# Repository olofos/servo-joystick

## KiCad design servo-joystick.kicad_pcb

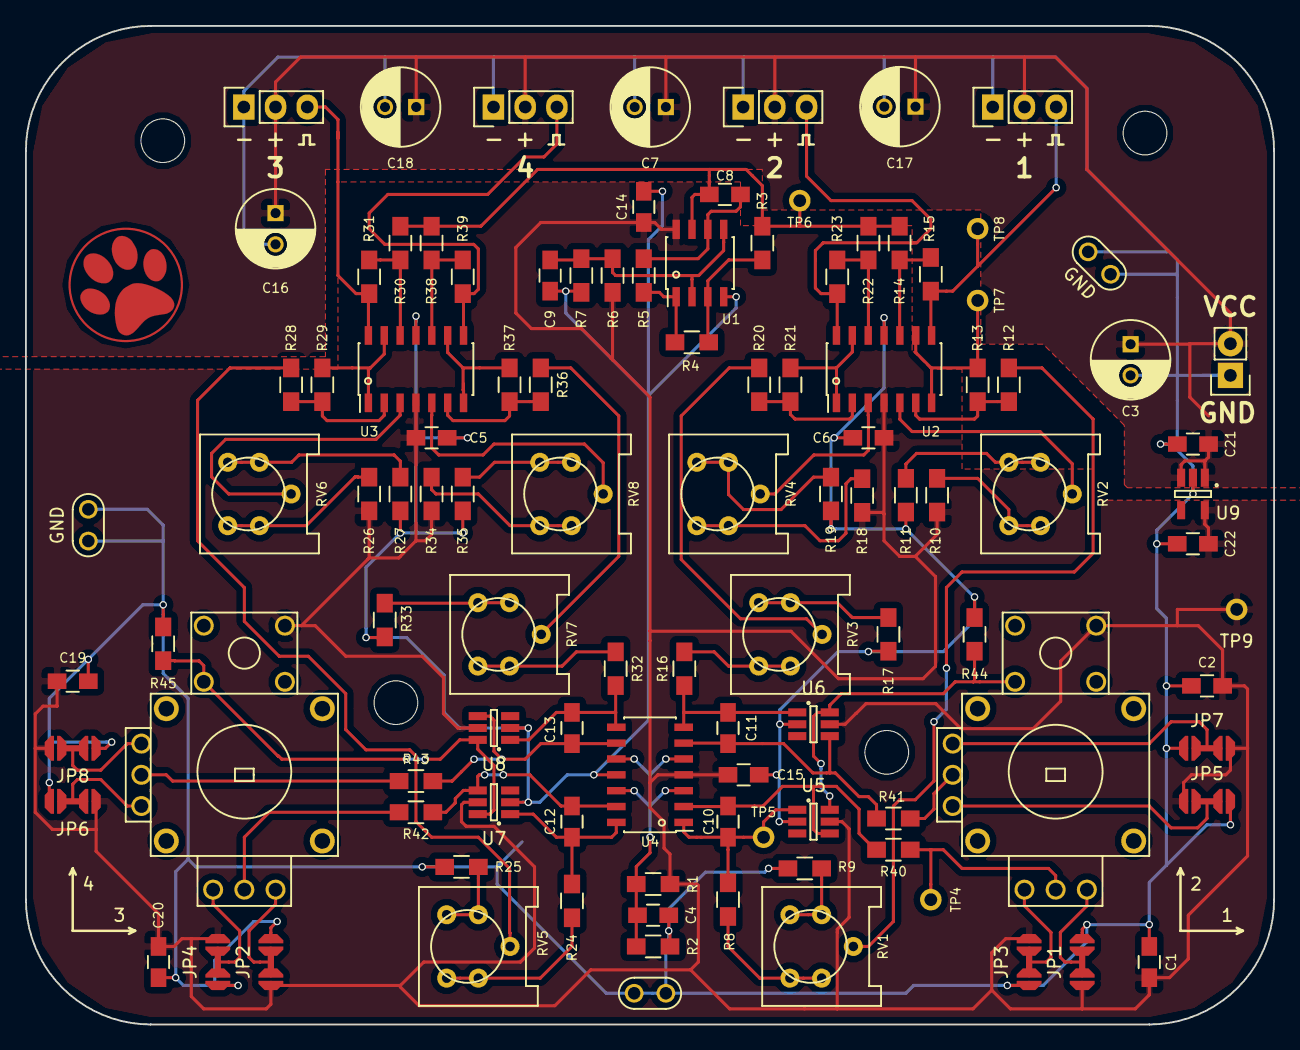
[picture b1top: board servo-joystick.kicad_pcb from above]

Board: 2 copper layers, 100.0 x 80.0 mm, 112 parts (0 on the bottom side), 71 nets.

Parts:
C1, C2, C4, C5, C6, C9, C14, C15, C19, C20: 1u; C_0805_HandSoldering
C3, C7, C16, C17, C18: 100u; C_Radial_D6.3_L11.2_P2.5
C8, C10, C11, C12, C13: 100n; C_0805_HandSoldering
C21, C22: 2u2; C_0805_HandSoldering
JP1, JP2, JP3, JP4, JP5, JP6, JP7, JP8: JUMPER-3
MH6, MH6#2, MH6#3, MH6#4: MOUNTING_HOLE; MH-M3
P1: CONN_01X02; Pin_Header_Straight_1x02
P2, P3, P4, P5: CONN_01X03; Pin_Header_Straight_1x03
R1, R2, R3, R6, R7, R44, R45: 1k2; R_0805_HandSoldering
R4: 3k; R_0805_HandSoldering
R5, R12, R13, R15, R20, R21, R23, R28, R29, R31, R36, R37, R39: 150k; R_0805_HandSoldering
R8, R10, R16, R18, R24, R26, R32, R34: 30k; R_0805_HandSoldering
R9, R14, R17, R22, R25, R30, R33, R38: 470; R_0805_HandSoldering
R11, R19, R27, R35: 15k; R_0805_HandSoldering
R40, R41, R42, R43: 6M8; R_0805_HandSoldering
RV1, RV3, RV5, RV7: 100; Potentiometer_Bourns_3386P
RV2, RV4, RV6, RV8: 1k; Potentiometer_Bourns_3386P
TP1, TP2, TP3: GND; TEST_POINT_DOUBLE_TH
TP4: CTRL1; TEST_POINT_THD_NO_CIRC
TP5: INT1; TEST_POINT_THD_NO_CIRC
TP6: SAW; TEST_POINT_THD_NO_CIRC
TP7: BUF1; TEST_POINT_THD_NO_CIRC
TP8: PWM1; TEST_POINT_THD_NO_CIRC
TP9: VCC; TEST_POINT_THD_NO_CIRC
U1: MCP6002; SOIC-8_3.9x4.9mm_Pitch1.27mm
U2, U3, U4: MCP6004; SOIC-14_3.9x8.7mm_Pitch1.27mm
U5, U6, U7, U8: SN74LVC1G3157; SOT-23-6-Handsoldering
U9: LD2981; SOT-23-5-Handsoldering
VR1, VR2: JOYSTICK_SW; F-JM10K

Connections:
+6V: C3.1, C7.1, C16.1, C17.1, C18.1, C21.1, P1.2, P2.2, P3.2, P4.2, P5.2, U9.1, U9.3
/Integrator #1/INT_FB: C10.2, R40.1, U4.2, U5.4
/Integrator #1/SW: R44.2, U5.6, U6.6, VR1.7
/Integrator #1/VIN: R40.2, TP4.1, VR1.2
/Integrator #1/VREF: C4.1, R1.2, R2.1, U4.3, U4.5, U4.10, U4.12
/Integrator #2/INT_FB: C11.2, R41.1, U4.6, U6.4
/Integrator #2/VIN: R41.2, VR1.5
/Integrator #3/INT_FB: C12.2, R42.1, U4.13, U7.4
/Integrator #3/SW: R45.2, U7.6, U8.6, VR2.7
/Integrator #3/VIN: R42.2, VR2.2
/Integrator #4/INT_FB: C13.2, R43.1, U4.9, U8.4
/Integrator #4/VIN: R43.2, VR2.5
/PWM #1/BUF: R13.1, TP7.1, U2.7, U2.9
/PWM #1/BUF_IN: R12.1, R13.2, U2.6
/PWM #1/PWM: P2.3, R15.1, TP8.1, U2.8
/PWM #1/SAWTOOTH: C8.1, R3.2, R14.2, R22.2, R30.2, R38.2, TP6.1, U1.7
/PWM #1/SAW_P: R14.1, R15.2, U2.10
/PWM #1/VIN: C10.1, R8.1, TP5.1, U4.1, U5.1
/PWM #1/VIN_ADJ_M: R9.1, RV1.3
/PWM #1/VIN_ADJ_P: R8.2, RV1.1
/PWM #1/VIN_DIV: R12.2, RV1.2
/PWM #1/VREF: RV2.2, U2.5
/PWM #1/VREF_ADJ_M: R11.1, RV2.3
/PWM #1/VREF_ADJ_P: R10.2, RV2.1
/PWM #2/BUF: R21.1, U2.1, U2.13
/PWM #2/BUF_IN: R20.1, R21.2, U2.2
/PWM #2/PWM: P3.3, R23.1, U2.14
/PWM #2/SAW_P: R22.1, R23.2, U2.12
/PWM #2/VIN: C11.1, R16.1, U4.7, U6.1
/PWM #2/VIN_ADJ_M: R17.1, RV3.3
/PWM #2/VIN_ADJ_P: R16.2, RV3.1
/PWM #2/VIN_DIV: R20.2, RV3.2
/PWM #2/VREF: RV4.2, U2.3
/PWM #2/VREF_ADJ_M: R19.1, RV4.3
/PWM #2/VREF_ADJ_P: R18.2, RV4.1
/PWM #3/BUF: R29.1, U3.1, U3.13
/PWM #3/BUF_IN: R28.1, R29.2, U3.2
/PWM #3/PWM: P4.3, R31.1, U3.14
/PWM #3/SAW_P: R30.1, R31.2, U3.12
/PWM #3/VIN: C12.1, R24.1, U4.14, U7.1
/PWM #3/VIN_ADJ_M: R25.1, RV5.3
/PWM #3/VIN_ADJ_P: R24.2, RV5.1
/PWM #3/VIN_DIV: R28.2, RV5.2
/PWM #3/VREF: RV6.2, U3.3
/PWM #3/VREF_ADJ_M: R27.1, RV6.3
/PWM #3/VREF_ADJ_P: R26.2, RV6.1
/PWM #4/BUF: R37.1, U3.7, U3.9
/PWM #4/BUF_IN: R36.1, R37.2, U3.6
/PWM #4/PWM: P5.3, R39.1, U3.8
/PWM #4/SAW_P: R38.1, R39.2, U3.10
/PWM #4/VIN: C13.1, R32.1, U4.8, U8.1
/PWM #4/VIN_ADJ_M: R33.1, RV7.3
/PWM #4/VIN_ADJ_P: R32.2, RV7.1
/PWM #4/VIN_DIV: R36.2, RV7.2
/PWM #4/VREF: RV8.2, U3.5
/PWM #4/VREF_ADJ_M: R35.1, RV8.3
/PWM #4/VREF_ADJ_P: R34.2, RV8.1
/Sawtooth Wave/COMP_FB: R3.1, R4.2, U1.3
/Sawtooth Wave/COMP_OUT: R4.1, R5.1, U1.1
/Sawtooth Wave/INT_IN: C8.2, R5.2, U1.6
/Sawtooth Wave/VREF: C9.2, R6.1, R7.2, U1.2, U1.5
GND: C1.2, C2.2, C3.2, C4.2, C5.2, C6.2, C7.2, C9.1, C14.2, C15.2, C16.2, C17.2, C18.2, C19.2, C20.2, C21.2, C22.2, JP1.3, JP2.3, JP3.1, JP4.1, JP5.3, JP6.3, JP7.1, JP8.1, P1.1, P2.1, P3.1, P4.1, P5.1, R2.2, R7.1, R9.2, R11.2, R17.2, R19.2, R25.2, R27.2, R33.2, R35.2, R44.1, R45.1, TP1.1, TP2.1, TP3.1, U1.4, U2.11, U3.11, U4.11, U5.2, U6.2, U7.2, U8.2, U9.2
unnamed: JP1.2, VR1.1
unnamed: JP2.2, VR2.1
unnamed: JP3.2, VR1.3
unnamed: JP4.2, VR2.3
unnamed: JP5.2, VR1.4
unnamed: JP6.2, VR2.4
unnamed: JP7.2, VR1.6
unnamed: JP8.2, VR2.6
VCC: C1.1, C2.1, C5.1, C6.1, C14.1, C15.1, C19.1, C20.1, C22.1, JP1.1, JP2.1, JP3.3, JP4.3, JP5.1, JP6.1, JP7.3, JP8.3, R1.1, R6.2, R10.1, R18.1, R26.1, R34.1, TP9.1, U1.8, U2.4, U3.4, U4.4, U5.5, U6.5, U7.5, U8.5, U9.5, VR1.10, VR2.10

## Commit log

2017-11-16 initial import
2018-06-10 Rev A
2018-06-11 Added 5V regulator
2018-06-11 Added missing foorprint for C3
2018-06-12 Removed 0R resistors and started new layout
2018-06-13 Larger SOT-23-6 pads
2018-06-13 Larger SOT-23-5 pads
2018-06-13 Better solder jumper footprint
2018-06-14 Correct pinout for LD2981
2018-06-14 Added cached component library
2018-06-14 Added .gitignore
2018-06-14 Fixed corner outline
